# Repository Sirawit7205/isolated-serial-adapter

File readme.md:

# Isolated Quad Serial Adapter

This is an open-source KiCAD design files for a four-channel isolated USB-to-Serial adapter based on CH344Q IC from WCH.

## Pictures

## Features

This adapter is convenient when you want to connect multiple serial devices to your computer simultaneously, while also provides isolation between your computer and those devices.

- Four USB-to-Serial channels
	- CH344Q IC: Only one USB required to communicate with all fours channels at the same time at maximum speed of 6Mbps.
	- 1024 bytes of RX FIFO buffer and 512 bytes of TX FIFO buffer per channel.
	- Configured as 2x RS485, 1x RS232, and 1x 5V UART channels.
	- Modem flow control signals for RS232 and UART.
	- Auto direction control for RS485.
	- RS485 120 Ohms termination resistors (on/off)
- Full Isolation
	- All power and data signals are fully isolated between the USB and the serial side.
	- CA-IS3088 dedicated RS485 isolation IC.
	- MAX3243 dedicated RS232 isolated IC (250kbps max).
	- Digital Isolator ICs for other signals.
	- UART voltage level selector (2.5/2.7/3.0/3.3/5.0 V)
	- 1W 5V isolated DC/DC converter.
- Other Protection
	- TVS diodes on all signals line, including the USB.
	- Polyfuse on USB VBUS.
- Intuitive Interfaces
	- USB Type-C Connector
	- Degson 3.5mm terminal blocks for serial channels
	- Pin header breakout for modem signals
	- RX/TX indicators
	- USB connection good indicator
	- Power indicators on both side of the isolation
	- USB reset and flow control mode buttons
	- Design to fit a 90x125x40mm PLC project box
	
## Revisions

We are currently at Revision 2. Changelog is below:

**Revision 1 (November 2022)**
 - Initial Design
 - U9 has wrong footprint (could still be soldered with some difficulties)
 
**Revision 2 (March 2024)**
 - Updated design for new enclosure
 - Updated circuit for more functionalities.
 - U11 has wrong Vref connection (do not populate)

## What is provided

The goal of this repository is to enable you to build this on your own as easy as possible. **The schematics, PCB design, and an interactive BOM is provided.**

Hardware is licensed under `SPDX-License-Identifier: CERN-OHL-S-2.0`

Contains no software

Documentation is licensed under `SPDX-License-Identifier: CC-BY-SA-4.0`

## Ordering

You can export gerbers from this project and order the board yourself. Noted that this board must be manufactured with 1.2mm thickness to fit the enclosure.

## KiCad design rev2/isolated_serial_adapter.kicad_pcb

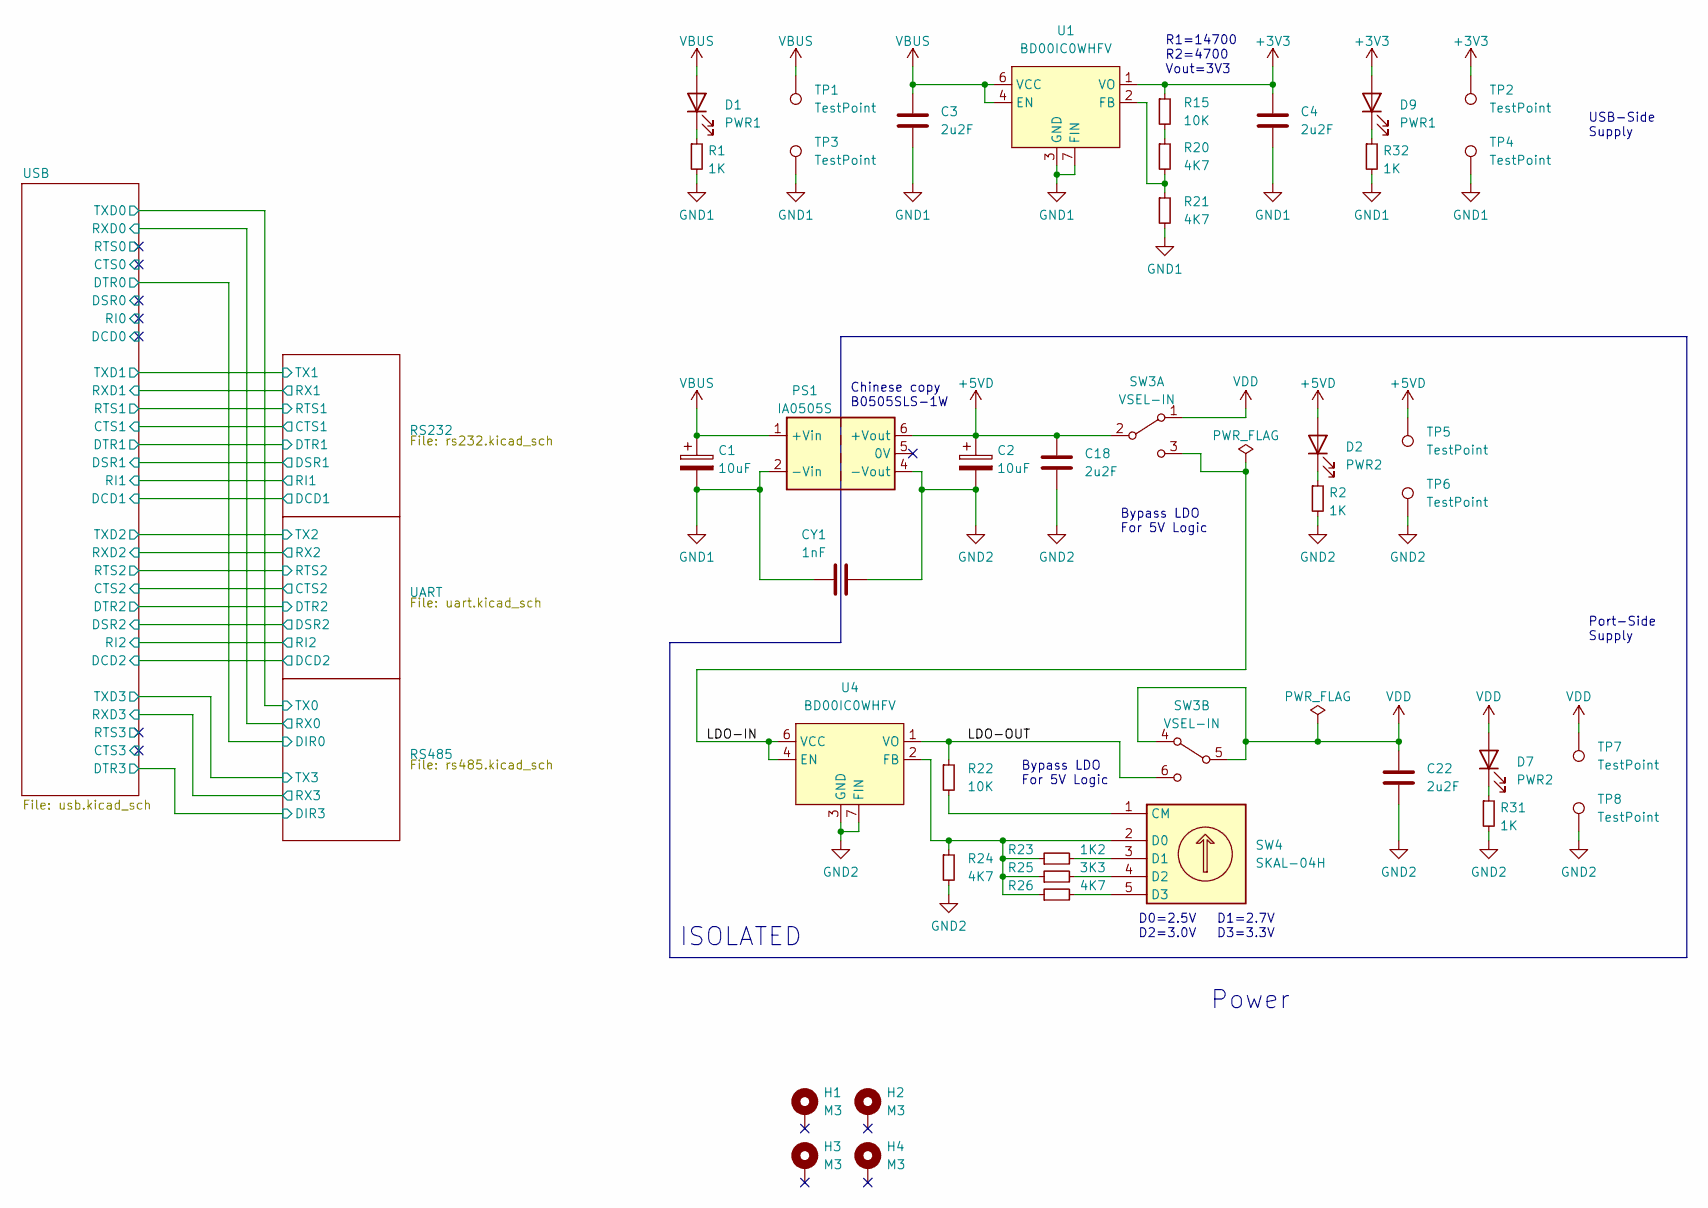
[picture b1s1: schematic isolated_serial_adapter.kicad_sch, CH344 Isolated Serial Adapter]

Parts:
C1, C2: 10uF; CP_Radial_D4.0mm_P1.50mm
C3, C4, C18, C22: 2u2F; C_0805_2012Metric
CY1: 1nF; C_Disc_D7.5mm_W5.0mm_P7.50mm
D1, D9: PWR1; LED_D3.0mm_Clear
D2, D7: PWR2; LED_D3.0mm_Clear
H1, H2, H3, H4: M3; MountingHole_3.2mm_M3_DIN965_Pad
PS1: IA0505S; Converter_DCDC_XP_POWER-IAxxxxS_THT
R1, R2, R31, R32: 1K; R_0603_1608Metric
R15, R22: 10K; R_0603_1608Metric
R20, R21, R24, R26: 4K7; R_0603_1608Metric
R23: 1K2; R_0603_1608Metric
R25: 3K3; R_0603_1608Metric
SW3: VSEL-IN; SW_DEALON_SK-22D02-G3_DPDT_Angled
SW4: SKAL-04H; SM_Switch_SKAL-04H
TP1, TP2, TP3, TP4, TP5, TP6, TP7, TP8: TestPoint; TestPoint_Pad_D1.0mm
U1, U4: BD00IC0WHFV; HVSOF6

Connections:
+3V3: C4.1, D9.2 (A), R15.1, TP2.1, U1.1 (VO); also elsewhere on the board
+5VD: C2.1, C18.1, D2.2 (A), PS1.6 (+Vout), SW3.2 (B), TP5.1; also elsewhere on the board
/LDO-IN: SW3.3 (C), U4.4 (EN), U4.6 (VCC)
/LDO-OUT: R22.1, SW3.6 (C), U4.1 (VO)
GND: C1.2, C3.2, C4.2, CY1.1, PS1.2 (-Vin), R1.2, R21.2, R32.2, TP3.1, TP4.1, U1.3 (GND), U1.7 (FIN); also elsewhere on the board
GND2: C2.2, C18.2, C22.2, CY1.2, PS1.4 (-Vout), R2.2, R24.2, R31.2, TP6.1, TP8.1, U4.3 (GND), U4.7 (FIN); also elsewhere on the board
unnamed: D1.1 (K), R1.1
unnamed: D2.1 (K), R2.1
unnamed: D7.1 (K), R31.1
unnamed: D9.1 (K), R32.1
unnamed: R15.2, R20.1
unnamed: R20.2, R21.1, U1.2 (FB)
unnamed: R22.2, SW4.1 (CM)
unnamed: R23.1, R24.1, R25.1, R26.1, SW4.2 (D0), U4.2 (FB)
unnamed: R23.2, SW4.3 (D1)
unnamed: R25.2, SW4.4 (D2)
unnamed: R26.2, SW4.5 (D3)
VBUS: C1.1, C3.1, D1.2 (A), PS1.1 (+Vin), TP1.1, U1.4 (EN), U1.6 (VCC); also elsewhere on the board
VDD: C22.1, D7.2 (A), SW3.1 (A), SW3.4 (A), SW3.5 (B), TP7.1; also elsewhere on the board

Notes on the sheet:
D0=2.5V D1=2.7V D2=3.0V D3=3.3V
ISOLATED
Power
Bypass LDO For 5V Logic
USB-Side Supply
R1=14700 R2=4700 Vout=3V3
Port-Side Supply
Chinese copy B0505SLS-1W

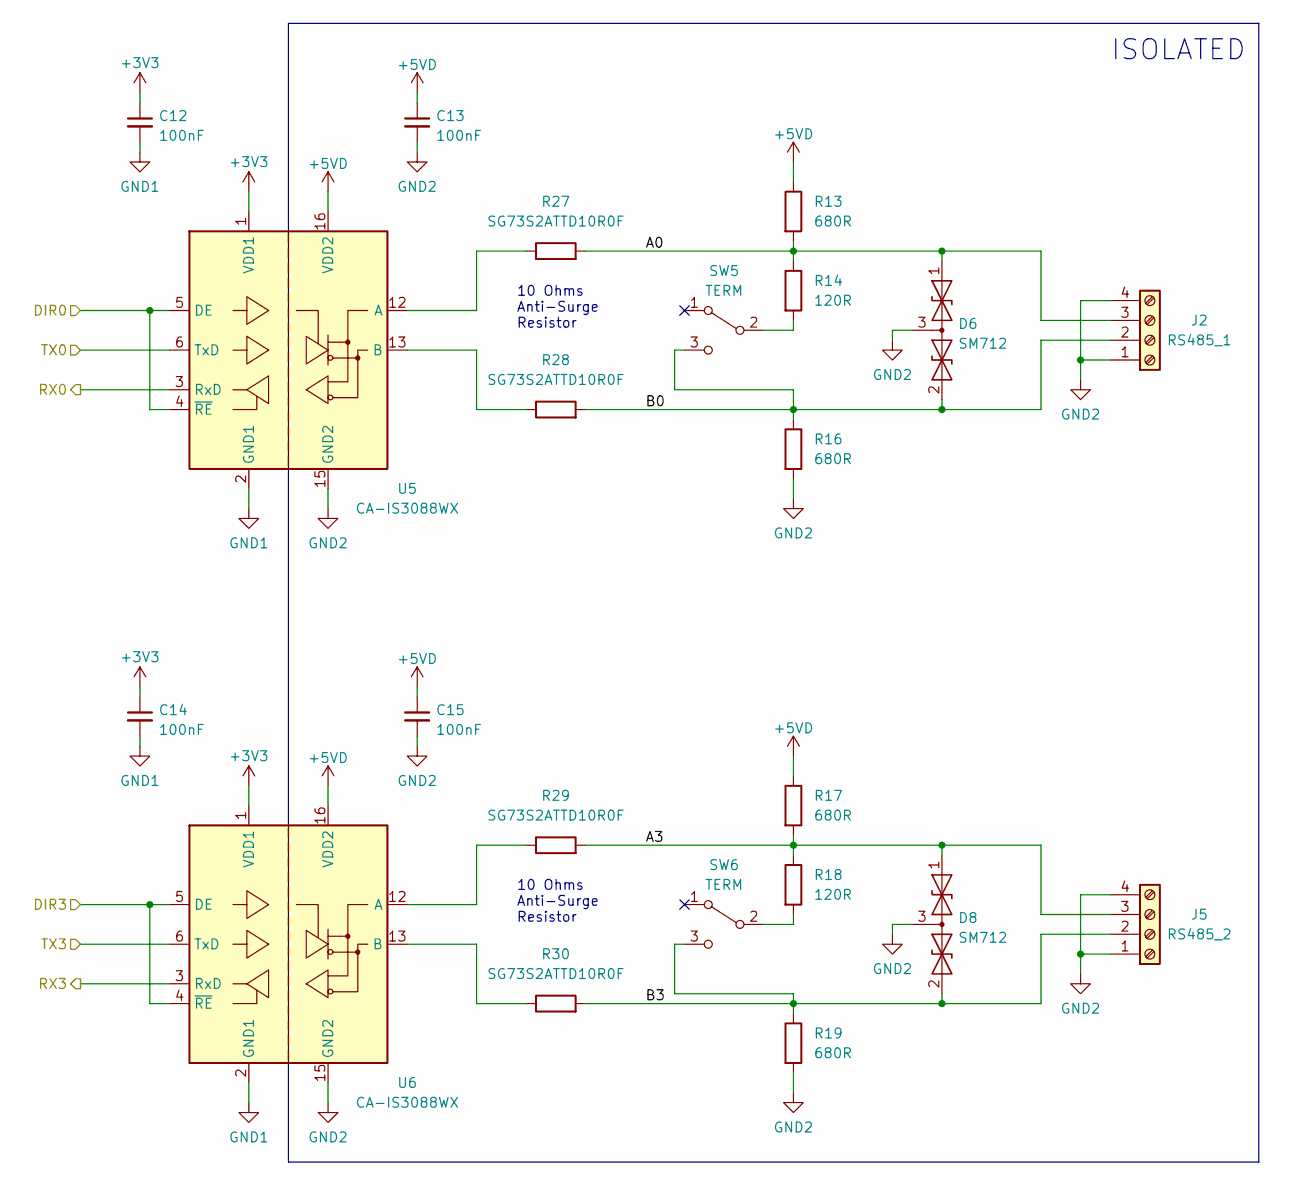
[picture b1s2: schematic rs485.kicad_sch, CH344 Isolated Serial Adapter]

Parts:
C12, C13, C14, C15: 100nF; C_0603_1608Metric
D6, D8: SM712; SOT-23
J2: RS485_1; TerminalBlock_Degson_1x04_P3.50mm_Horizontal
J5: RS485_2; TerminalBlock_Degson_1x04_P3.50mm_Horizontal
R13, R16, R17, R19: 680R; R_0603_1608Metric
R14, R18: 120R; R_0603_1608Metric
R27, R28, R29, R30: SG73S2ATTD10R0F; R_0805_2012Metric
SW5, SW6: TERM; SW_CuK_OS102011MA1QN1_SPDT_Angled
U5, U6: CA-IS3088WX; SOIC-16W_7.5x10.3mm_P1.27mm

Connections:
+3V3: C12.1, C14.1, U5.1 (VDD1), U6.1 (VDD1); also elsewhere on the board
+5VD: C13.1, C15.1, R13.1, R17.1, U5.16 (VDD2), U6.16 (VDD2); also elsewhere on the board
/RS485/A0: D6.1 (A1), J2.3, R13.2, R14.1, R27.2
/RS485/A3: D8.1 (A1), J5.3, R17.2, R18.1, R29.2
/RS485/B0: D6.2 (A2), J2.2, R16.1, R28.2, SW5.3 (C)
/RS485/B3: D8.2 (A2), J5.2, R19.1, R30.2, SW6.3 (C)
/RS485/DIR0: U5.4 (~RE), U5.5 (DE); also elsewhere on the board
/RS485/DIR3: U6.4 (~RE), U6.5 (DE); also elsewhere on the board
/RS485/RX0: U5.3 (RxD); also elsewhere on the board
/RS485/RX3: U6.3 (RxD); also elsewhere on the board
/RS485/TX0: U5.6 (TxD); also elsewhere on the board
/RS485/TX3: U6.6 (TxD); also elsewhere on the board
GND: C12.2, C14.2, U5.2 (GND1), U5.7 (GND1), U5.8 (GND1), U6.2 (GND1), U6.7 (GND1), U6.8 (GND1); also elsewhere on the board
GND2: C13.2, C15.2, D6.3 (common), D8.3 (common), J2.1, J2.4, J5.1, J5.4, R16.2, R19.2, U5.9 (GND2), U5.10 (GND2), U5.15 (GND2), U6.9 (GND2), U6.10 (GND2), U6.15 (GND2); also elsewhere on the board
unnamed: R14.2, SW5.2 (B)
unnamed: R18.2, SW6.2 (B)
unnamed: R27.1, U5.12 (A)
unnamed: R28.1, U5.13 (B)
unnamed: R29.1, U6.12 (A)
unnamed: R30.1, U6.13 (B)

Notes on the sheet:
10 Ohms Anti-Surge Resistor
ISOLATED

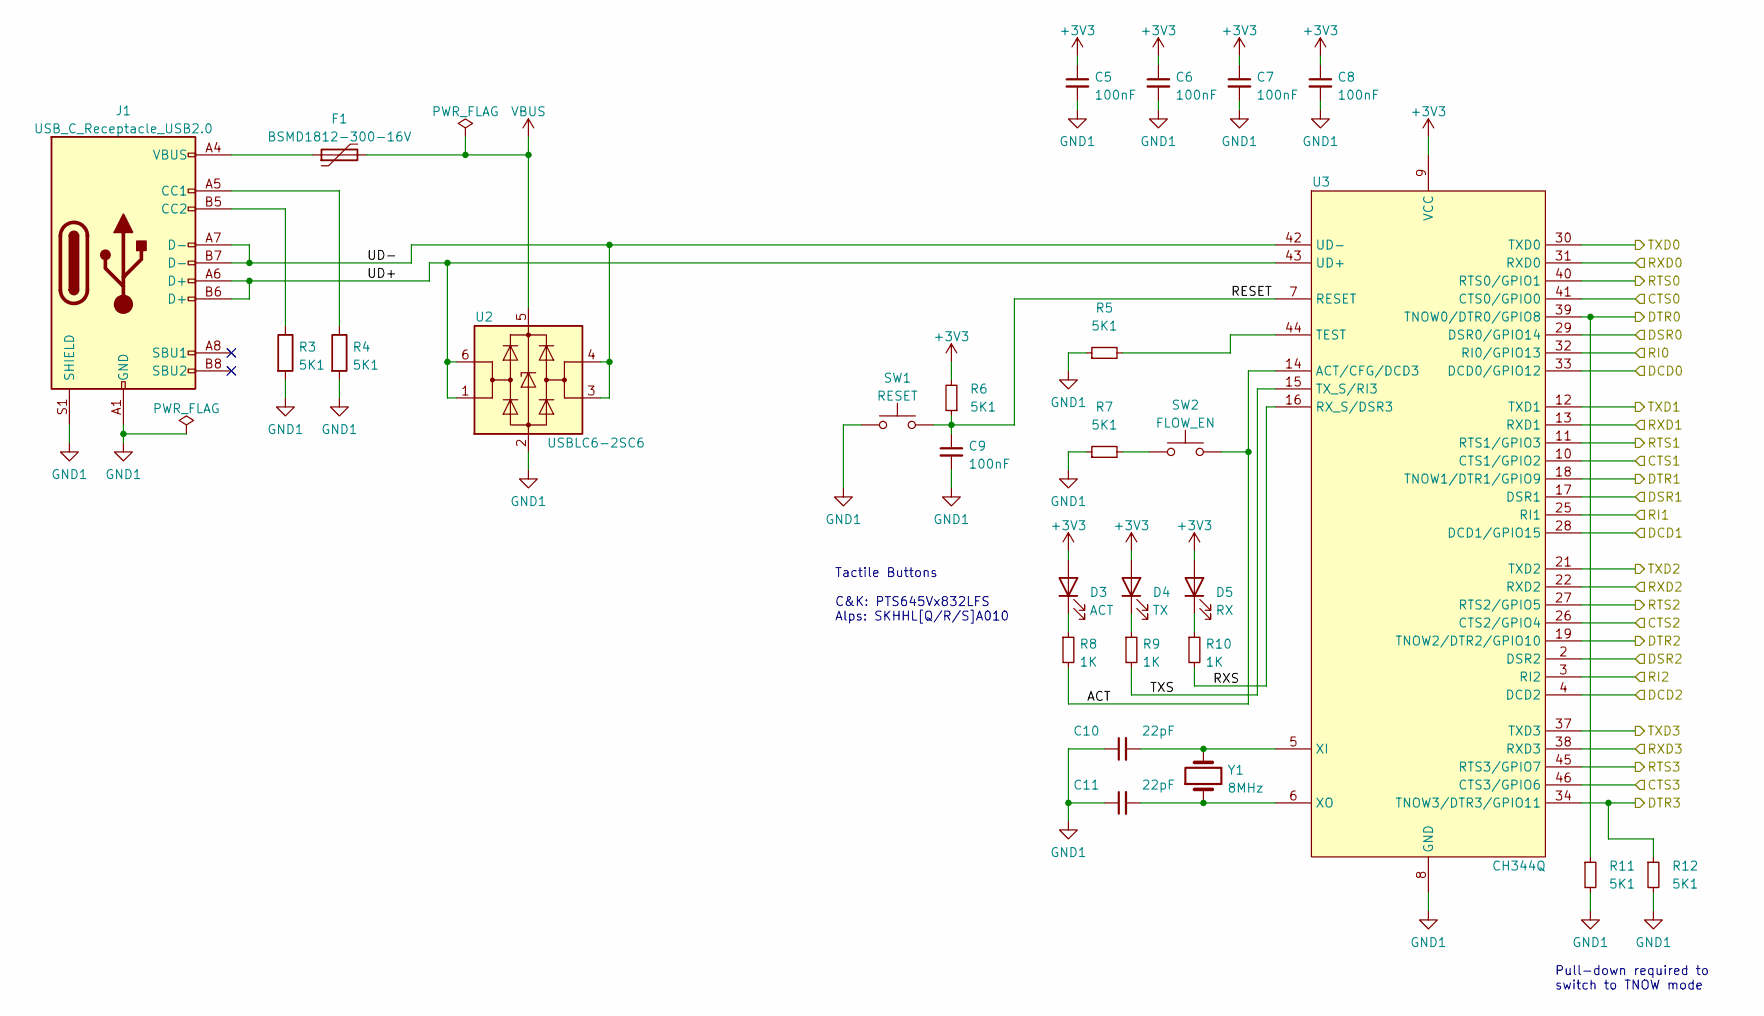
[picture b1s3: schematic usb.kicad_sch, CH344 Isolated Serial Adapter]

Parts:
C5, C6, C7, C8, C9: 100nF; C_0603_1608Metric
C10, C11: 22pF; C_0603_1608Metric
D3: ACT; LED_D3.0mm_Clear
D4: TX; LED_D3.0mm_Clear
D5: RX; LED_D3.0mm_Clear
F1: BSMD1812-300-16V; Fuse_1812_4532Metric
J1: USB_C_Receptacle_USB2.0; USB_C_Receptacle_HRO_TYPE-C-31-M-12_NO_SBU
R3, R4, R5, R6, R7, R11, R12: 5K1; R_0603_1608Metric
R8, R9, R10: 1K; R_0603_1608Metric
SW1: RESET; SW_Tactile_SPST_Angled_PTS645Vx83-2LFS
SW2: FLOW_EN; SW_Tactile_SPST_Angled_PTS645Vx83-2LFS
U2: USBLC6-2SC6; SOT-23-6
U3: CH344Q; LQFP-48_7x7mm_P0.5mm
Y1: 8MHz; Crystal_SMD_5032-2Pin_5.0x3.2mm

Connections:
+3V3: C5.1, C6.1, C7.1, C8.1, D3.2 (A), D4.2 (A), D5.2 (A), R6.2, U3.9 (VCC), U3.24 (VCC), U3.36 (VCC), U3.48 (VCC); also elsewhere on the board
/RS232/CTS1: U3.10 (CTS1/GPIO2); also elsewhere on the board
/RS232/DCD1: U3.28 (DCD1/GPIO15); also elsewhere on the board
/RS232/DSR1: U3.17 (DSR1); also elsewhere on the board
/RS232/DTR1: U3.18 (TNOW1/DTR1/GPIO9); also elsewhere on the board
/RS232/RI1: U3.25 (RI1); also elsewhere on the board
/RS232/RTS1: U3.11 (RTS1/GPIO3); also elsewhere on the board
/RS232/RX1: U3.13 (RXD1); also elsewhere on the board
/RS232/TX1: U3.12 (TXD1); also elsewhere on the board
/RS485/DIR0: R11.1, U3.39 (TNOW0/DTR0/GPIO8); also elsewhere on the board
/RS485/DIR3: R12.1, U3.34 (TNOW3/DTR3/GPIO11); also elsewhere on the board
/RS485/RX0: U3.31 (RXD0); also elsewhere on the board
/RS485/RX3: U3.38 (RXD3); also elsewhere on the board
/RS485/TX0: U3.30 (TXD0); also elsewhere on the board
/RS485/TX3: U3.37 (TXD3); also elsewhere on the board
/UART/CTS2: U3.26 (CTS2/GPIO4); also elsewhere on the board
/UART/DCD2: U3.4 (DCD2); also elsewhere on the board
/UART/DSR2: U3.2 (DSR2); also elsewhere on the board
/UART/DTR2: U3.19 (TNOW2/DTR2/GPIO10); also elsewhere on the board
/UART/RI2: U3.3 (RI2); also elsewhere on the board
/UART/RTS2: U3.27 (RTS2/GPIO5); also elsewhere on the board
/UART/RX2: U3.22 (RXD2); also elsewhere on the board
/UART/TX2: U3.21 (TXD2); also elsewhere on the board
/USB/ACT: R8.2, SW2.2, U3.14 (ACT/CFG/DCD3)
/USB/CTS0: U3.41 (CTS0/GPIO0)
/USB/CTS3: U3.46 (CTS3/GPIO6)
/USB/DCD0: U3.33 (DCD0/GPIO12)
/USB/DSR0: U3.29 (DSR0/GPIO14)
/USB/RESET: C9.1, R6.1, SW1.2, U3.7 (RESET)
/USB/RI0: U3.32 (RI0/GPIO13)
/USB/RTS0: U3.40 (RTS0/GPIO1)
/USB/RTS3: U3.45 (RTS3/GPIO7)
/USB/RXS: R10.2, U3.16 (RX_S/DSR3)
/USB/TXS: R9.2, U3.15 (TX_S/RI3)
/USB/UD+: J1.A6 (D+), J1.B6 (D+), U2.1 (I/O1), U2.6 (I/O1), U3.43 (UD+)
/USB/UD-: J1.A7 (D-), J1.B7 (D-), U2.3 (I/O2), U2.4 (I/O2), U3.42 (UD-)
GND: C5.2, C6.2, C7.2, C8.2, C9.2, C10.1, C11.1, J1.A1 (GND), J1.A12 (GND), J1.B1 (GND), J1.B12 (GND), J1.S1 (SHIELD), R3.2, R4.2, R5.1, R7.1, R11.2, R12.2, SW1.1, U2.2 (GND), U3.8 (GND), U3.20 (GND), U3.23 (GND), U3.35 (GND), U3.47 (GND); also elsewhere on the board
unnamed: C10.2, U3.5 (XI), Y1.2
unnamed: C11.2, U3.6 (XO), Y1.1
unnamed: D3.1 (K), R8.1
unnamed: D4.1 (K), R9.1
unnamed: D5.1 (K), R10.1
unnamed: F1.1, J1.A4 (VBUS), J1.A9 (VBUS), J1.B4 (VBUS), J1.B9 (VBUS)
unnamed: J1.A5 (CC1), R4.1
unnamed: J1.B5 (CC2), R3.1
unnamed: R5.2, U3.44 (TEST)
unnamed: R7.2, SW2.1
VBUS: F1.2, U2.5 (VBUS); also elsewhere on the board

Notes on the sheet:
Tactile Buttons C&K: PTS645Vx832LFS Alps: SKHHL[Q/R/S]A010
Pull-down required to switch to TNOW mode

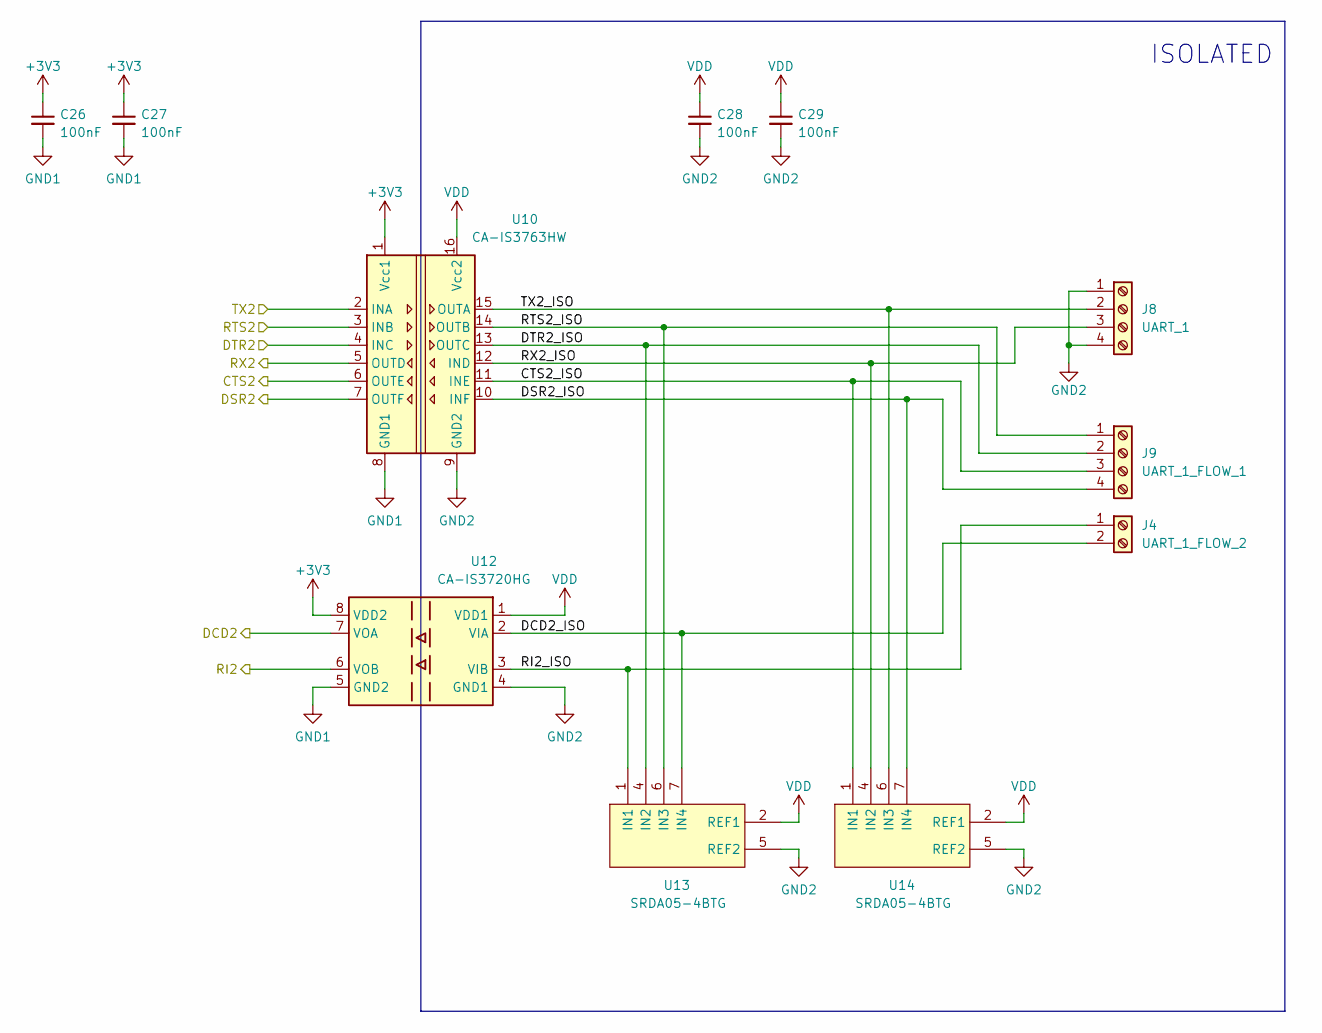
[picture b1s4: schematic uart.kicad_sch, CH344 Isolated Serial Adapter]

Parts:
C26, C27, C28, C29: 100nF; C_0603_1608Metric
J4: UART_1_FLOW_2; TerminalBlock_Degson_1x02_P3.50mm_Horizontal
J8: UART_1; TerminalBlock_Degson_1x04_P3.50mm_Horizontal
J9: UART_1_FLOW_1; TerminalBlock_Degson_1x04_P3.50mm_Horizontal
U10: CA-IS3763HW; SOIC-16W_7.5x10.3mm_P1.27mm
U12: CA-IS3720HG; SOIC-8_7.5x5.85mm_P1.27mm
U13, U14: SRDA05-4BTG; SOIC-8_3.9x4.9mm_P1.27mm

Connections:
+3V3: C26.1, C27.1, U10.1 (Vcc1), U12.8 (VDD2); also elsewhere on the board
/UART/CTS2: U10.6 (OUTE); also elsewhere on the board
/UART/CTS2_ISO: J9.3, U10.11 (INE), U14.1 (IN1)
/UART/DCD2: U12.7 (VOA); also elsewhere on the board
/UART/DCD2_ISO: J4.2, U12.2 (VIA), U13.7 (IN4)
/UART/DSR2: U10.7 (OUTF); also elsewhere on the board
/UART/DSR2_ISO: J9.4, U10.10 (INF), U14.7 (IN4)
/UART/DTR2: U10.4 (INC); also elsewhere on the board
/UART/DTR2_ISO: J9.2, U10.13 (OUTC), U13.4 (IN2)
/UART/RI2: U12.6 (VOB); also elsewhere on the board
/UART/RI2_ISO: J4.1, U12.3 (VIB), U13.1 (IN1)
/UART/RTS2: U10.3 (INB); also elsewhere on the board
/UART/RTS2_ISO: J9.1, U10.14 (OUTB), U13.6 (IN3)
/UART/RX2: U10.5 (OUTD); also elsewhere on the board
/UART/RX2_ISO: J8.3, U10.12 (IND), U14.4 (IN2)
/UART/TX2: U10.2 (INA); also elsewhere on the board
/UART/TX2_ISO: J8.2, U10.15 (OUTA), U14.6 (IN3)
GND: C26.2, C27.2, U10.8 (GND1), U12.5 (GND2); also elsewhere on the board
GND2: C28.2, C29.2, J8.1, J8.4, U10.9 (GND2), U12.4 (GND1), U13.5 (REF2), U13.8 (REF2), U14.5 (REF2), U14.8 (REF2); also elsewhere on the board
VDD: C28.1, C29.1, U10.16 (Vcc2), U12.1 (VDD1), U13.2 (REF1), U13.3 (REF1), U14.2 (REF1), U14.3 (REF1); also elsewhere on the board

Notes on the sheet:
ISOLATED

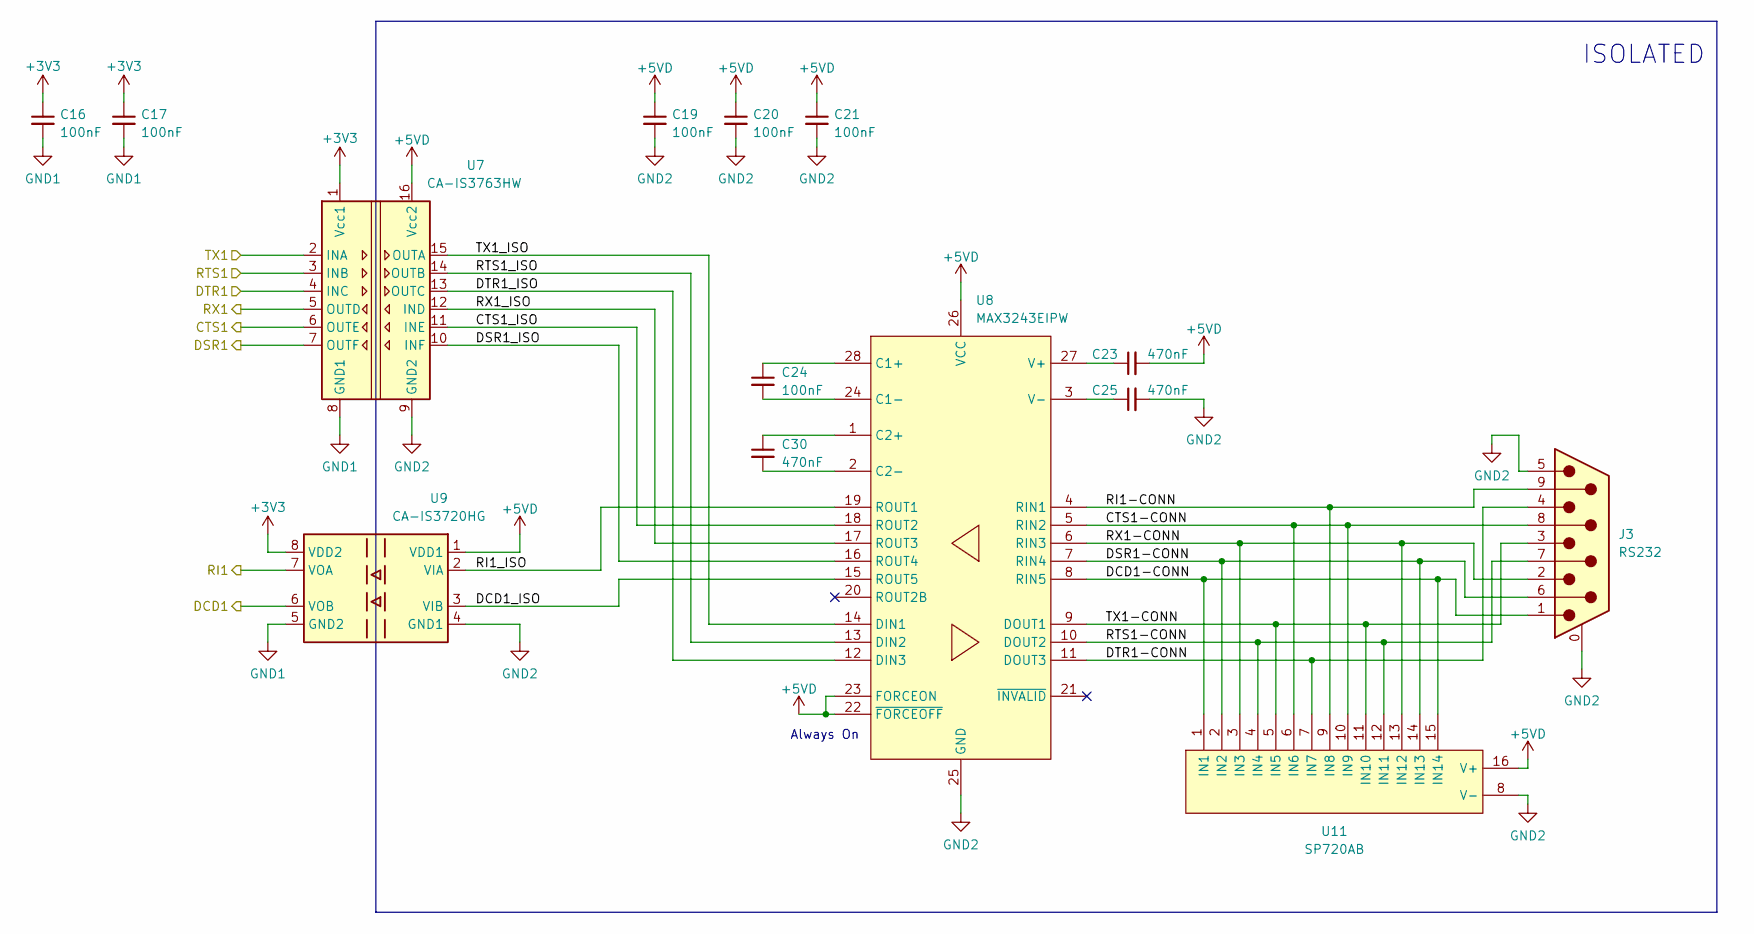
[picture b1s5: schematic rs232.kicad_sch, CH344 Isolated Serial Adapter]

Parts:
C16, C17, C19, C20, C21, C24: 100nF; C_0603_1608Metric
C23, C25, C30: 470nF; C_0603_1608Metric
J3: RS232; DSUB-9_Male_Horizontal_P2.77x2.84mm_EdgePinOffset7.70mm_Hou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
U7: CA-IS3763HW; SOIC-16W_7.5x10.3mm_P1.27mm
U8: MAX3243EIPW; TSSOP-28_4.4x9.7mm_P0.65mm
U9: CA-IS3720HG; SOIC-8_7.5x5.85mm_P1.27mm
U11: SP720AB; SOIC-16_3.9x9.9mm_P1.27mm

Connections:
+3V3: C16.1, C17.1, U7.1 (Vcc1), U9.8 (VDD2); also elsewhere on the board
+5VD: C19.1, C20.1, C21.1, C23.2, U7.16 (Vcc2), U8.22 (~FORCEOFF), U8.23 (FORCEON), U8.26 (VCC), U9.1 (VDD1), U11.16 (V+); also elsewhere on the board
/RS232/CTS1: U7.6 (OUTE); also elsewhere on the board
/RS232/CTS1-CONN: J3.8, U8.5 (RIN2), U11.6 (IN6), U11.10 (IN9)
/RS232/CTS1_ISO: U7.11 (INE), U8.18 (ROUT2)
/RS232/DCD1: U9.6 (VOB); also elsewhere on the board
/RS232/DCD1-CONN: J3.1, U8.8 (RIN5), U11.1 (IN1), U11.15 (IN14)
/RS232/DCD1_ISO: U8.15 (ROUT5), U9.3 (VIB)
/RS232/DSR1: U7.7 (OUTF); also elsewhere on the board
/RS232/DSR1-CONN: J3.6, U8.7 (RIN4), U11.2 (IN2), U11.14 (IN13)
/RS232/DSR1_ISO: U7.10 (INF), U8.16 (ROUT4)
/RS232/DTR1: U7.4 (INC); also elsewhere on the board
/RS232/DTR1-CONN: J3.4, U8.11 (DOUT3), U11.7 (IN7)
/RS232/DTR1_ISO: U7.13 (OUTC), U8.12 (DIN3)
/RS232/RI1: U9.7 (VOA); also elsewhere on the board
/RS232/RI1-CONN: J3.9, U8.4 (RIN1), U11.9 (IN8)
/RS232/RI1_ISO: U8.19 (ROUT1), U9.2 (VIA)
/RS232/RTS1: U7.3 (INB); also elsewhere on the board
/RS232/RTS1-CONN: J3.7, U8.10 (DOUT2), U11.4 (IN4), U11.12 (IN11)
/RS232/RTS1_ISO: U7.14 (OUTB), U8.13 (DIN2)
/RS232/RX1: U7.5 (OUTD); also elsewhere on the board
/RS232/RX1-CONN: J3.2, U8.6 (RIN3), U11.3 (IN3), U11.13 (IN12)
/RS232/RX1_ISO: U7.12 (IND), U8.17 (ROUT3)
/RS232/TX1: U7.2 (INA); also elsewhere on the board
/RS232/TX1-CONN: J3.3, U8.9 (DOUT1), U11.5 (IN5), U11.11 (IN10)
/RS232/TX1_ISO: U7.15 (OUTA), U8.14 (DIN1)
GND: C16.2, C17.2, U7.8 (GND1), U9.5 (GND2); also elsewhere on the board
GND2: C19.2, C20.2, C21.2, C25.2, J3.0 (PAD), J3.5, U7.9 (GND2), U8.25 (GND), U9.4 (GND1), U11.8 (V-); also elsewhere on the board
unnamed: C23.1, U8.27 (V+)
unnamed: C24.1, U8.28 (C1+)
unnamed: C24.2, U8.24 (C1-)
unnamed: C25.1, U8.3 (V-)
unnamed: C30.1, U8.1 (C2+)
unnamed: C30.2, U8.2 (C2-)

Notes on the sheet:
Always On
ISOLATED

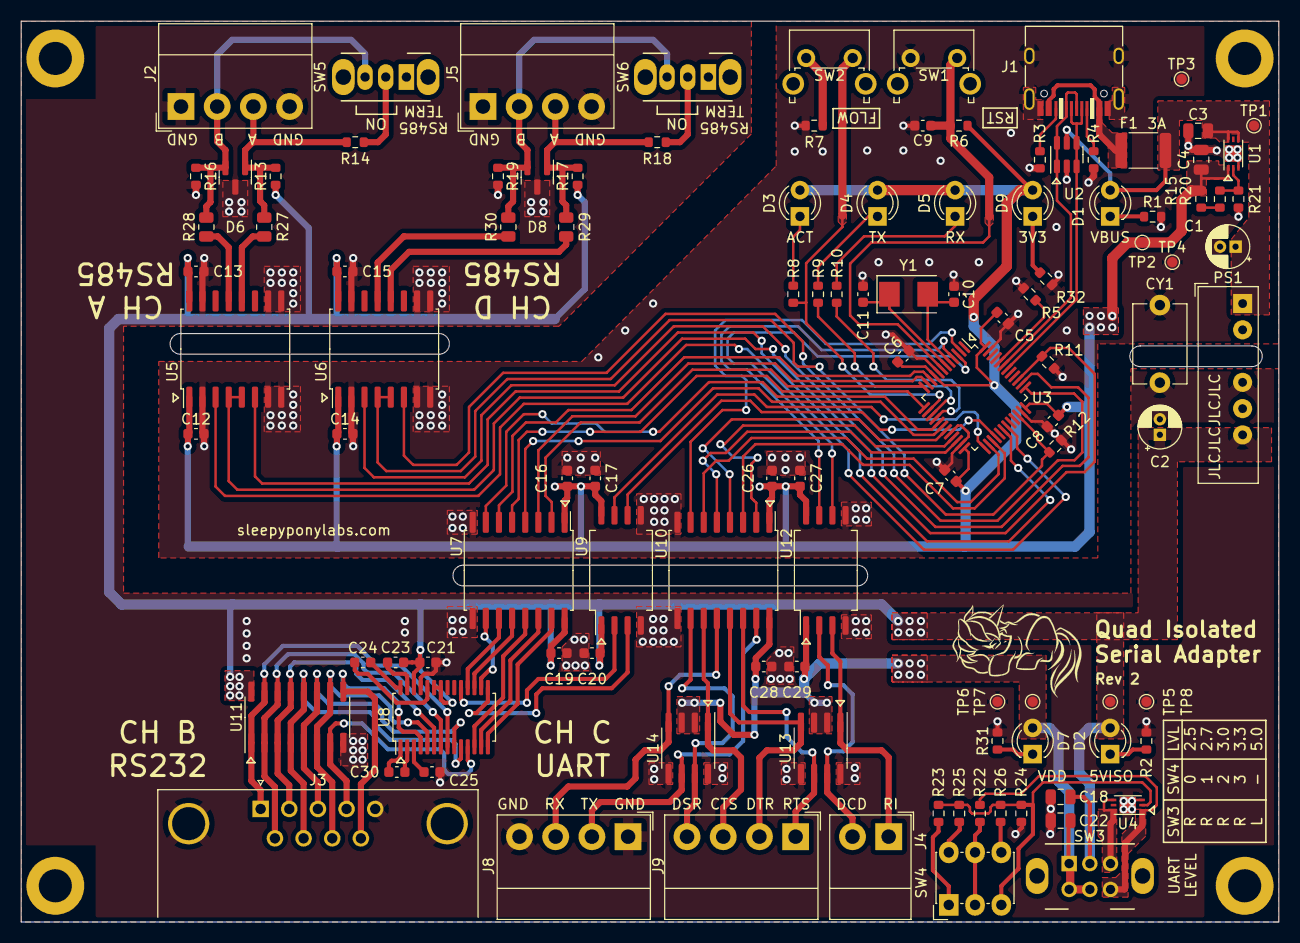
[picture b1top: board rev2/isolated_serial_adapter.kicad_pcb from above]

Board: 2 copper layers, 121.6 x 87.1 mm, 114 parts (0 on the bottom side), 97 nets.

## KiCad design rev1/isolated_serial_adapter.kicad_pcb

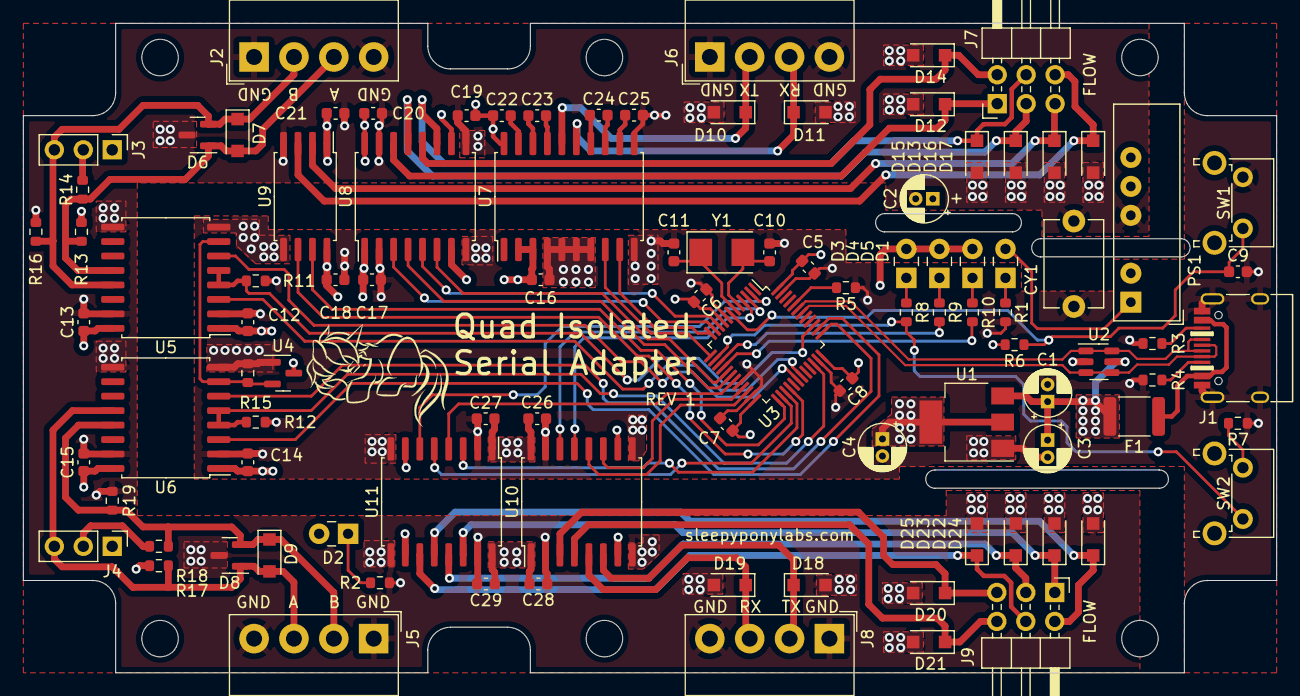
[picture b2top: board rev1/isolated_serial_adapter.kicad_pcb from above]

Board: 4 copper layers, 110.0 x 57.0 mm, 105 parts (0 on the bottom side), 74 nets.

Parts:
C1, C2, C3, C4: 10uF; CP_Radial_D4.0mm_P1.50mm
C5, C6, C7, C8, C9, C12, C13, C14, C15, C16, C17, C18, C19, C20, C21, C22, C23, C24, C25, C26, C27, C28, C29: 100nF; C_0603_1608Metric
C10, C11: 22pF; C_0603_1608Metric
CY1: 1nF; C_Disc_D7.5mm_W5.0mm_P7.50mm
D1: PWR1; LED_Rectangular_W3.0mm_H2.0mm
D2: PWR2; LED_Rectangular_W3.0mm_H2.0mm
D3: ACT; LED_Rectangular_W3.0mm_H2.0mm
D4: TX; LED_Rectangular_W3.0mm_H2.0mm
D5: RX; LED_Rectangular_W3.0mm_H2.0mm
D6, D8: SM712; SOT-23
D7, D9: SMF12CA; D_SOD-123F
D10, D11, D12, D13, D14, D15, D16, D17, D18, D19, D20, D21, D22, D23, D24, D25: SMF15CA; D_SOD-123F
F1: BSMD1812-300-16V; Fuse_1812_4532Metric
H1, H2, H3, H4, H5, H6: M3; MountingHole_3.2mm_M3
J1: USB_C_Receptacle_USB2.0; USB_C_Receptacle_HRO_TYPE-C-31-M-12_NO_SBU
J2: RS485_1; TerminalBlock_Degson_1x04_P3.50mm_Horizontal
J3, J4: TERM; PinHeader_1x03_P2.54mm_Vertical
J5: RS485_2; TerminalBlock_Degson_1x04_P3.50mm_Horizontal
J6: RS232_1; TerminalBlock_Degson_1x04_P3.50mm_Horizontal
J7: RS232_1_FLOW; PinHeader_2x03_P2.54mm_Horizontal
J8: UART_1; TerminalBlock_Degson_1x04_P3.50mm_Horizontal
J9: UART_1_FLOW; PinHeader_2x03_P2.54mm_Horizontal
PS1: IA0505S; Converter_DCDC_XP_POWER-IAxxxxS_THT
R1, R2, R8, R9, R10: 1K; R_0603_1608Metric
R3, R4, R5, R6, R7, R11, R12: 5K1; R_0603_1608Metric
R13, R16, R17, R19: 680R; R_0603_1608Metric
R14, R18: 120R; R_0603_1608Metric
R15: 100K; R_0603_1608Metric
SW1: RESET; SW_Tactile_SPST_Angled_PTS645Vx83-2LFS
SW2: FLOW_EN; SW_Tactile_SPST_Angled_PTS645Vx83-2LFS
U1: AMS1117-3.3; SOT-223-3_TabPin2
U2: USBLC6-2SC6; SOT-23-6
U3: CH344Q; LQFP-48_7x7mm_P0.5mm
U4: LM809R; SOT-23
U5, U6: ADM2483BRWZ; SOIC-16W_7.5x10.3mm_P1.27mm
U7: ADM3251E; SOIC-20W_7.5x12.8mm_P1.27mm
U8, U11: CA-IS3742HW; SOIC-16W_7.5x10.3mm_P1.27mm
U9: CA-IS3720HG; SOIC-8_7.5x5.85mm_P1.27mm_modified
U10: CA-IS3741HW; SOIC-16W_7.5x10.3mm_P1.27mm
Y1: 8MHz; Crystal_SMD_5032-2Pin_5.0x3.2mm

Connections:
+3V3: C4.1, C5.1, C6.1, C7.1, C8.1, C12.1, C14.1, C16.1, C17.1, C18.1, C26.1, C27.1, D3.2 (A), D4.2 (A), D5.2 (A), R6.2, U1.2 (VO), U3.9 (VCC), U3.24 (VCC), U3.36 (VCC), U3.48 (VCC), U4.3 (VCC), U5.1 (VDD1), U6.1 (VDD1), U7.2 (VCC), U7.3 (VCC), U8.1 (VDD1), U8.7 (VE1), U9.8 (VDD2), U10.10 (VE2), U10.16 (VDD2), U11.1 (VDD1), U11.7 (VE1)
+5VD: C2.1, C13.1, C15.1, C19.1, C20.1, C21.1, C22.1, C28.1, C29.1, D2.2 (A), PS1.6 (+Vout), R13.1, R17.1, U5.16 (VDD2), U6.16 (VDD2), U7.20 (VCC_ISO), U8.10 (VE2), U8.16 (VDD2), U9.1 (VDD1), U10.1 (VDD1), U10.7 (VE1), U11.10 (VE2), U11.16 (VDD2)
/RS232/CTS1: U3.10 (CTS1/GPIO2), U8.5 (VOC)
/RS232/CTS1_ISO: D14.1 (A1), J7.2, U8.12 (VIC)
/RS232/DCD1: U3.28 (DCD1/GPIO15), U9.6 (VOB)
/RS232/DCD1_ISO: D17.1 (A1), J7.6, U9.3 (VIB)
/RS232/DSR1: U3.17 (DSR1), U8.6 (VOD)
/RS232/DSR1_ISO: D15.1 (A1), J7.4, U8.11 (VID)
/RS232/DTR1: U3.18 (TNOW1/DTR1/GPIO9), U8.4 (VIB)
/RS232/DTR1_ISO: D13.1 (A1), J7.3, U8.13 (VOB)
/RS232/RI1: U3.25 (RI1), U9.7 (VOA)
/RS232/RI1_ISO: D16.1 (A1), J7.5, U9.2 (VIA)
/RS232/RTS1: U3.11 (RTS1/GPIO3), U8.3 (VIA)
/RS232/RTS1_ISO: D12.1 (A1), J7.1, U8.14 (VOA)
/RS232/RX1: U3.13 (RXD1), U7.8 (R_OUT)
/RS232/RX1_ISO: D11.1 (A1), J6.3, U7.15 (R_IN)
/RS232/TX1: U3.12 (TXD1), U7.9 (T_IN)
/RS232/TX1_ISO: D10.1 (A1), J6.2, U7.16 (T_OUT)
/RS485/A0: D6.1 (A1), D7.2 (A2), J2.3, R13.2, R14.1, U5.12 (A)
/RS485/A3: D8.1 (A1), D9.2 (A2), J4.3, J5.3, R17.2, U6.12 (A)
/RS485/B0: D6.2 (A2), D7.1 (A1), J2.2, J3.3, R16.1, U5.13 (B)
/RS485/B3: D8.2 (A2), D9.1 (A1), J5.2, R18.2, R19.1, U6.13 (B)
/RS485/DIR0: R11.1, U3.39 (TNOW0/DTR0/GPIO8), U5.4 (~RE), U5.5 (DE)
/RS485/DIR3: R12.1, U3.34 (TNOW3/DTR3/GPIO11), U6.4 (~RE), U6.5 (DE)
/RS485/RX0: U3.31 (RXD0), U5.3 (RxD)
/RS485/RX3: U3.38 (RXD3), U6.3 (RxD)
/RS485/TX0: U3.30 (TXD0), U5.6 (TxD)
/RS485/TX3: U3.37 (TXD3), U6.6 (TxD)
/RS485/~RESET: R15.1, U4.2 (~RESET), U5.7 (PV), U6.7 (PV)
/UART/CTS2: U3.26 (CTS2/GPIO4), U11.5 (VOC)
/UART/CTS2_ISO: D24.1 (A1), J9.2, U11.12 (VIC)
/UART/DCD2: U3.4 (DCD2), U10.13 (VOB)
/UART/DCD2_ISO: D21.1 (A1), J9.6, U10.4 (VIB)
/UART/DSR2: U3.2 (DSR2), U11.6 (VOD)
/UART/DSR2_ISO: D25.1 (A1), J9.4, U11.11 (VID)
/UART/DTR2: U3.19 (TNOW2/DTR2/GPIO10), U11.4 (VIB)
/UART/DTR2_ISO: D23.1 (A1), J9.3, U11.13 (VOB)
/UART/RI2: U3.3 (RI2), U10.14 (VOA)
/UART/RI2_ISO: D20.1 (A1), J9.5, U10.3 (VIA)
/UART/RTS2: U3.27 (RTS2/GPIO5), U11.3 (VIA)
/UART/RTS2_ISO: D22.1 (A1), J9.1, U11.14 (VOA)
/UART/RX2: U3.22 (RXD2), U10.12 (VOC)
/UART/RX2_ISO: D19.1 (A1), J8.3, U10.5 (VIC)
/UART/TX2: U3.21 (TXD2), U10.11 (VID)
/UART/TX2_ISO: D18.1 (A1), J8.2, U10.6 (VOD)
/USB/ACT: R8.2, SW2.2, U3.14 (ACT/CFG)
/USB/RXS: R10.2, U3.16 (RX_S)
/USB/TXS: R9.2, U3.15 (TX_S)
/USB/UD+: J1.A6 (D+), J1.B6 (D+), U2.1 (I/O1), U2.6 (I/O1), U3.43 (UD+)
/USB/UD-: J1.A7 (D-), J1.B7 (D-), U2.3 (I/O2), U2.4 (I/O2), U3.42 (UD-)
GND: C1.2, C3.2, C4.2, C5.2, C6.2, C7.2, C8.2, C9.2, C10.1, C11.1, C12.2, C14.2, C16.2, C17.2, C18.2, C26.2, C27.2, CY1.1, J1.A1 (GND), J1.A12 (GND), J1.B1 (GND), J1.B12 (GND), J1.S1 (SHIELD), PS1.2 (-Vin), R1.2, R3.2, R4.2, R5.1, R7.1, R11.2, R12.2, R15.2, SW1.1, U1.1 (GND), U2.2 (GND), U3.8 (GND), U3.20 (GND), U3.23 (GND), U3.35 (GND), U3.47 (GND), U4.1 (GND), U5.2 (GND1), U5.8 (GND1), U6.2 (GND1), U6.8 (GND1), U7.4 (GND), U7.5 (GND), U7.6 (GND), U7.7 (GND), U7.10 (GND), U8.2 (GND1), U8.8 (GND1), U9.5 (GND2), U10.9 (GND2), U10.15 (GND2), U11.2 (GND1), U11.8 (GND1)
GND2: C2.2, C13.2, C15.2, C19.2, C20.2, C21.2, C25.2, C28.2, C29.2, CY1.2, D6.3 (common), D8.3 (common), D10.2 (A2), D11.2 (A2), D12.2 (A2), D13.2 (A2), D14.2 (A2), D15.2 (A2), D16.2 (A2), D17.2 (A2), D18.2 (A2), D19.2 (A2), D20.2 (A2), D21.2 (A2), D22.2 (A2), D23.2 (A2), D24.2 (A2), D25.2 (A2), J2.1, J2.4, J5.1, J5.4, J6.1, J6.4, J8.1, J8.4, PS1.4 (-Vout), R2.2, R16.2, R19.2, U5.9 (GND2), U5.15 (GND2), U6.9 (GND2), U6.15 (GND2), U7.11 (GND_ISO), U8.9 (GND2), U8.15 (GND2), U9.4 (GND1), U10.2 (GND1), U10.8 (GND1), U11.9 (GND2), U11.15 (GND2)
unnamed: C9.1, R6.1, SW1.2, U3.7 (RESET)
unnamed: C10.2, U3.5 (XI), Y1.2
unnamed: C11.2, U3.6 (XO), Y1.1
unnamed: C22.2, U7.19 (V+)
unnamed: C23.1, U7.18 (C1+)
unnamed: C23.2, U7.17 (C1-)
unnamed: C24.1, U7.14 (C2+)
unnamed: C24.2, U7.13 (C2-)
unnamed: C25.1, U7.12 (V-)
unnamed: D1.1 (K), R1.1
unnamed: D2.1 (K), R2.1
unnamed: D3.1 (K), R8.1
unnamed: D4.1 (K), R9.1
unnamed: D5.1 (K), R10.1
unnamed: F1.1, J1.A4 (VBUS), J1.A9 (VBUS), J1.B4 (VBUS), J1.B9 (VBUS)
unnamed: J1.A5 (CC1), R4.1
unnamed: J1.B5 (CC2), R3.1
unnamed: J3.2, R14.2
unnamed: J4.2, R18.1
unnamed: R5.2, U3.44 (TEST)
unnamed: R7.2, SW2.1
VBUS: C1.1, C3.1, D1.2 (A), F1.2, PS1.1 (+Vin), U1.3 (VI), U2.5 (VBUS)

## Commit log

2022-11-07 Fix incorrect standoff clearances
2022-11-07 Fix NPTH and edge milling dimensions
2023-05-28 Add readme, edit license
2024-01-10 Rearrange the repo
2024-02-09 WIP Revision 2 board
2024-03-06 Final Rev 2 Design
2025-03-12 Add front panel design
2025-03-22 Fixed front panel graphics
